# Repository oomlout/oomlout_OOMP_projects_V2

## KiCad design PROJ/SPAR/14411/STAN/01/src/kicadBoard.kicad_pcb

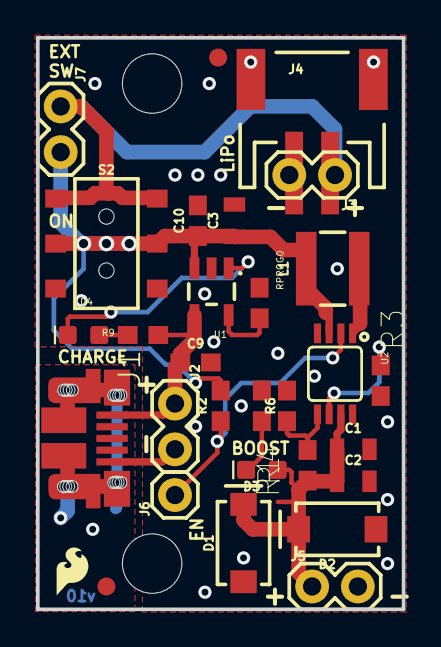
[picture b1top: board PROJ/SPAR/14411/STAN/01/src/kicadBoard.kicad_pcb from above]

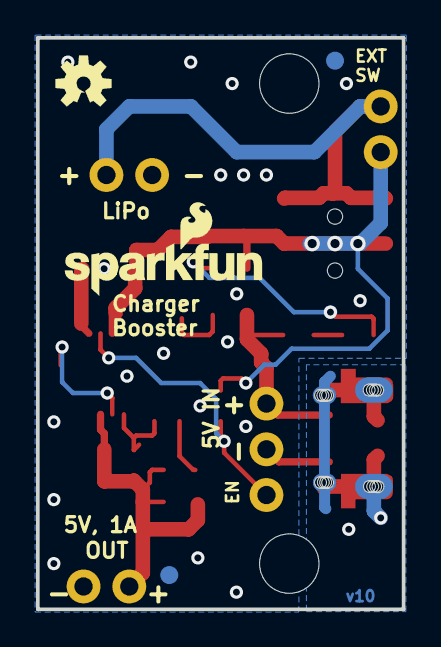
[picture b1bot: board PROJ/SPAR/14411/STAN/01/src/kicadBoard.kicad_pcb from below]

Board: 2 copper layers, 20.3 x 31.8 mm, 38 parts (5 on the bottom side), 14 nets.

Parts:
C1, C2, C3: 22uF; 0805
C9, C10: 4.7uF; 0603
D1, D2: 3A/40V/500mV; SMA-DIODE
D3: RED; LED-0603
D4: BLUE; LED-0603
FRAME1: FRAME-LETTER; CREATIVE_COMMONS
J1: AMP FCI 10103594-0001LF; USB-MICROB-PTH
J2, J3, J7: PTH; 1X02
J4: JST; JST-2-SMD
J5: 1X02
J6: 1X01
JP1, JP2, JP4, JP16: FIDUCIAL1X2; FIDUCIAL-1X2
JP3: SFE_LOGO_NAME_FLAME.1_INCH; SFE_LOGO_NAME_FLAME_.1
JP6, JP7: STAND-OFF
L1: 2.2UH3A; INDUCTOR_4X4MM
LOGO1: SFE_LOGO_FLAME.1_INCH; SFE_LOGO_FLAME_.1
R1: 100k; 0603
R2, R4: 750K; 0603
R3: DNP; 0603
R6: 4.7k; 0603
R9: 1k; 0603
RPROG0: 2.0k; 0603
S2: SWITCH_DPDT_SMD_AYZ0202
TP1: TEST-POINT3; PAD.03X.03
U1: MCP73831; SOT23-5
U2: PAM2401; MSOP8
U$1: OSHW-LOGOS; OSHW-LOGO-S

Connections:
5VIN: C9.1, J1.VBUS, J2.1, R9.2, U1.4
EN: J6.1, R2.1, U2.2
GND: C1.2, C2.2, C3.2, C9.2, C10.2, D1.A, D2.A, J1.GND, J2.2, J3.2, J4.1, J5.2, R1.1, R3.1, R6.1, RPROG0.2, U1.2, U2.4, U2.8
unnamed: D3.C, R6.2
unnamed: D4.A, R9.1
unnamed: L1.P$2, U2.1
unnamed: R3.2, U2.6
unnamed: J3.1, J4.2, J7.1, S2.1, S2.4
unnamed: RPROG0.1, U1.5
unnamed: R1.2, R4.1, U2.5
unnamed: D4.C, TP1.P$1, U1.1
SHIELD: J1.P$1, J1.P$2, J1.P$3, J1.P$4, J1.P$6, J1.P$8, J1.P$10, J1.P$12, J1.SHEILD2, J1.SHIELD, J1.SHIELD3, J1.SHIELD4
VBATT: C3.1, C10.1, J7.2, L1.P$1, R2.2, S2.2, S2.5, U1.3, U2.3
VCC: C1.1, C2.1, D1.C, D2.C, D3.A, J5.1, R4.2, U2.7

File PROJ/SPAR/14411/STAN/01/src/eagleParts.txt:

Partlist

Exported from boardEagle.brd at 19/08/2022 23:57

EAGLE Version 9.6.2 Copyright (c) 1988-2020 Autodesk, Inc.

Assembly variant: 

Part     Value                   Package                 Library               Position (inch)       Orientation

C1       22uF                    0805                    SparkFun-Capacitors   (0.69 0.35)           R0
C2       22uF                    0805                    SparkFun-Capacitors   (0.69 0.28)           R0
C3       22uF                    0805                    SparkFun-Capacitors   (0.43 0.85)           R90
C9       4.7uF                   0603                    SparkFun-Capacitors   (0.345 0.54)          R0
C10      4.7uF                   0603                    SparkFun-Capacitors   (0.35 0.85)           R90
D1       3A/40V/500mV            SMA-DIODE               SparkFun-DiscreteSemi (0.45 0.145)          R90
D2       3A/40V/500mV            SMA-DIODE               SparkFun-DiscreteSemi (0.655 0.175)         R180
D3       RED                     LED-0603                SparkFun-LED          (0.49 0.305)          R180
D4       BLUE                    LED-0603                SparkFun-LED          (0.1 0.6)             R180
J1       AMP FCI 10103594-0001LF USB-MICROB-PTH          SparkFun-Connectors   (0.11 0.375)          R270
J2       PTH                     1X02                    SparkFun-Connectors   (0.3 0.45)            R270
J3       PTH                     1X02                    SparkFun-Connectors   (0.65 0.95)           R180
J4       JST                     JST-2-SMD               SparkFun-Connectors   (0.6 1.1)             R0
J5                               1X02                    SparkFun-Connectors   (0.6 0.05)            R0
J6                               1X01                    SparkFun-Connectors   (0.3 0.25)            R90
J7       PTH                     1X02                    SparkFun-Connectors   (0.05 1.1)            R270
JP1      FIDUCIAL1X2             FIDUCIAL-1X2            SparkFun-Aesthetics   (0.15 1.2)            MR0
JP2      FIDUCIAL1X2             FIDUCIAL-1X2            SparkFun-Aesthetics   (0.15 0.05)           R0
JP4      FIDUCIAL1X2             FIDUCIAL-1X2            SparkFun-Aesthetics   (0.5125 0.075)        MR0
JP16     FIDUCIAL1X2             FIDUCIAL-1X2            SparkFun-Aesthetics   (0.394375 1.206875)   R0
L1       2.2UH3A                 INDUCTOR_4X4MM          SparkFun-Coils        (0.645 0.745)         R90
R1       100k                    0603                    SparkFun-Resistors    (0.545 0.445)         R270
R2       750K                    0603                    SparkFun-Resistors    (0.4 0.445)           R90
R3       DNP                     0603                    SparkFun-Resistors    (0.75 0.5)            R90
R4       750K                    0603                    SparkFun-Resistors    (0.59 0.315)          R270
R6       4.7k                    0603                    SparkFun-Resistors    (0.49 0.445)          R270
R9       1k                      0603                    SparkFun-Resistors    (0.23 0.6)            R0
RPROG    2.0k                    0603                    SparkFun-Resistors    (0.485 0.67)          R90
S2                               SWITCH_DPDT_SMD_AYZ0202 SparkFun-Switches     (0.15 0.8)            R270
TP1      TEST-POINT3             PAD.03X.03              SparkFun-Connectors   (0.16 0.65)           MR0
U1       MCP73831                SOT23-5                 SparkFun-IC-Power     (0.38 0.695)          R180
U2       PAM2401                 MSOP8                   SparkFun-IC-Power     (0.65 0.515)          R180

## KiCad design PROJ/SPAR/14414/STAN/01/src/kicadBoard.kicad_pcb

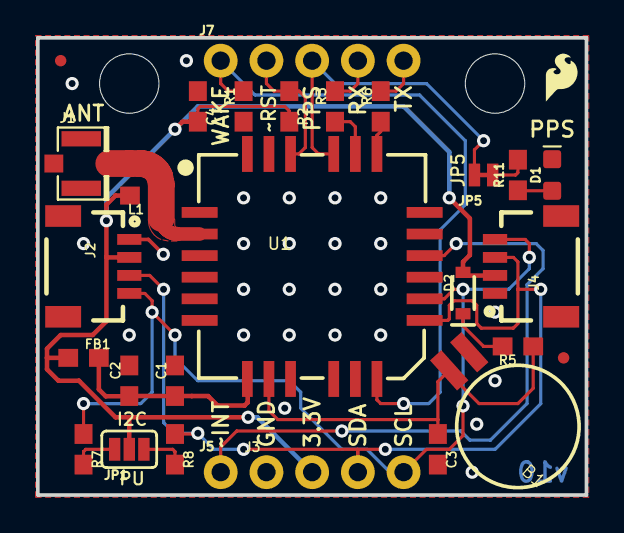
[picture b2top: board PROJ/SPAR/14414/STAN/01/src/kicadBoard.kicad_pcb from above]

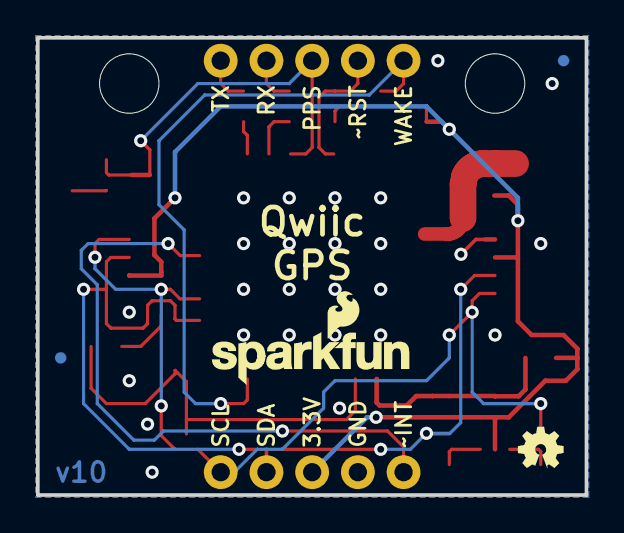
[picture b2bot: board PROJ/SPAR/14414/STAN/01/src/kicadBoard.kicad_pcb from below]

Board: 2 copper layers, 30.5 x 25.4 mm, 38 parts (4 on the bottom side), 20 nets.

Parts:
B1: 6.8MM_COIN_CELL; BATTCON-6.8MM
C1: 0.1uF; 0603
C2, C3, C4: 1.0uF; 0603
D1: BLUE; LED-0603
D2: 0.5A/40V/420mV; SOD-323
FB1: 600Ohm/100MHz; 0603
FRAME1: FRAME-LETTER; CREATIVE_COMMONS
J1: U.FL
J2, J4: Qwiic Right Angle; 1X04_1MM_RA
J3: PTH; 1X04_NO_SILK
J5: 1X01_NO_SILK
J7: 1X05_NO_SILK
JP1: SMT-JUMPER_3_2-NC_PASTE_SILK
JP2, JP6, JP7, JP8: FIDUCIALUFIDUCIAL; MICRO-FIDUCIAL
JP3, JP4: STAND-OFF
JP5: SMT-JUMPER_2_NC_TRACE_NO-SILK
L1: 33nH/±5%/500mA; 0603
LOGO1: OSHW-LOGOMINI; OSHW-LOGO-MINI
LOGO2: SFE_LOGO_NAME_FLAME.1_INCH; SFE_LOGO_NAME_FLAME_.1
LOGO3: REVISION
R1, R2: 10k; 0603
R3, R6, R11: 470; 0603
R5: 1k; 0603
R7, R8: 4.7k; 0603
U1: Titan X1 GPS; TITAN_X1_GPS
U$2: SFE_LOGO_FLAME_.1
U$3: SPECIAL_INSTRUCTIONS-PRODUCTION; PRODUCTION_INSTRUCTIONS

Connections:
3.3V: C4.2, D2.A, FB1.1, J2.2, J3.2, J4.2, JP1.2, L1.2, R2.2
BACKUP: B1.+, C3.1, R5.1, U1.8
EXT_ANT: J1.FEED, L1.1, U1.2
GND: B1.-, C1.2, C2.2, C3.2, C4.1, D1.C, J1.1, J1.2, J2.1, J3.1, J4.1, R1.1, U1.1, U1.3, U1.4, U1.5, U1.6, U1.9, U1.10, U1.11, U1.24
INT: J5.1, U1.16
unnamed: D1.A, R11.1
unnamed: JP5.1, R11.2
unnamed: JP1.1, R8.2
unnamed: D2.C, R5.2
unnamed: JP1.3, R7.2
PPS: J7.3, JP5.2, U1.21
RX: J7.4, R3.2
RXLV: R3.1, U1.20
SCL: J2.4, J3.4, J4.4, R7.1, U1.14
SDA: J2.3, J3.3, J4.3, R8.1, U1.13
TX: J7.5, R6.2
TXLV: R6.1, U1.19
VCC_FILTERED: C1.1, C2.1, FB1.2, U1.7
WAKE: J7.1, R1.2, U1.12
~RESET: J7.2, R2.1, U1.22

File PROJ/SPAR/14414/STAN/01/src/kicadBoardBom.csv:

"Id";"Designator";"Package";"Quantity";"Designation";"Supplier and ref";
1;"JP1";"SMT-JUMPER_3_2-NC_PASTE_SILK";1;"";;;
2;"R11,R6,R3";"0603";3;"470";;;
3;"JP6,JP2,JP7,JP8";"MICRO-FIDUCIAL";4;"FIDUCIALUFIDUCIAL";;;
4;"L1";"0603";1;"33nH/±5%/500mA";;;
5;"U$3";"PRODUCTION_INSTRUCTIONS";1;"SPECIAL_INSTRUCTIONS-PRODUCTION";;;
6;"U$2";"SFE_LOGO_FLAME_.1";1;"";;;
7;"J1";"U.FL";1;"U.FL";;;
8;"J4,J2";"1X04_1MM_RA";2;"Qwiic Right Angle";;;
9;"D1";"LED-0603";1;"BLUE";;;
10;"R1,R2";"0603";2;"10k";;;
11;"C3,C2,C4";"0603";3;"1.0uF";;;
12;"LOGO3";"REVISION";1;"REVISION";;;
13;"R8,R7";"0603";2;"4.7k";;;
14;"FRAME1";"CREATIVE_COMMONS";1;"FRAME-LETTER";;;
15;"B1";"BATTCON-6.8MM";1;"6.8MM_COIN_CELL";;;
16;"U1";"TITAN_X1_GPS";1;"Titan X1 GPS";;;
17;"JP5";"SMT-JUMPER_2_NC_TRACE_NO-SILK";1;"";;;
18;"J5";"1X01_NO_SILK";1;"";;;
19;"JP4,JP3";"STAND-OFF";2;"STAND-OFF";;;
20;"R5";"0603";1;"1k";;;
21;"J3";"1X04_NO_SILK";1;"PTH";;;
22;"C1";"0603";1;"0.1uF";;;
23;"FB1";"0603";1;"600Ohm/100MHz";;;
24;"J7";"1X05_NO_SILK";1;"";;;
25;"D2";"SOD-323";1;"0.5A/40V/420mV";;;
26;"LOGO2";"SFE_LOGO_NAME_FLAME_.1";1;"SFE_LOGO_NAME_FLAME.1_INCH";;;
27;"LOGO1";"OSHW-LOGO-MINI";1;"OSHW-LOGOMINI";;;

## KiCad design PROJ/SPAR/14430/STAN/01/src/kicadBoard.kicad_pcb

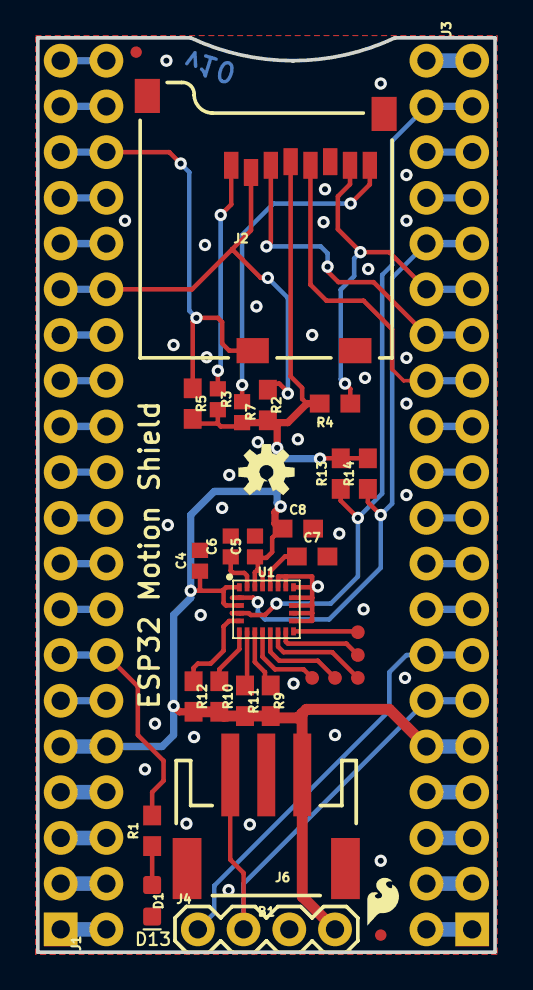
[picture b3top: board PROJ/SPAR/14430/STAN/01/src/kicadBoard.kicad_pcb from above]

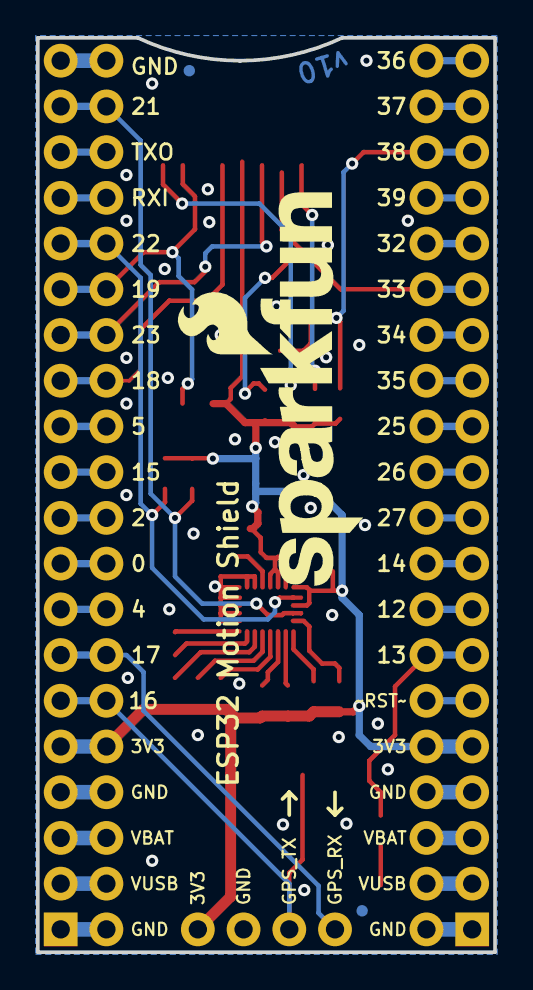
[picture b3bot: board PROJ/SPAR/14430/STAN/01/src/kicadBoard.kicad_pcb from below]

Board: 2 copper layers, 25.4 x 50.8 mm, 38 parts (3 on the bottom side), 49 nets.

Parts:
B1: ESP32_THING_WO_ANT_KEEPOUT; ESP32_THING_NO_ANT
C4, C5, C6: 0.1uF; 0402
C7: 10nF; 0603
C8: 10uF; 0603
D1: BLUE; LED-0603
FD1, FD2, FD3, FD4: FIDUCIALUFIDUCIAL; FIDUCIAL-MICRO
FRAME1: FRAME-LETTER; CREATIVE_COMMONS
J1, J3: 1X20_NOSILK
J2: MICRO-SD_CARD_SOCKET; MICRO-SD-SOCKET
J4: 1X04
J6: 3-PIN SMD; JST-3-SMD
LOGO1: OSHW-LOGOS; OSHW-LOGO-S
LOGO2: SFE_LOGO_NAME_FLAME.2_INCH; SFE_LOGO_NAME_FLAME_.2
LOGO3: SFE_LOGO_FLAME.1_INCH; SFE_LOGO_FLAME_.1
R1: 470; 0603
R2, R4, R5, R9, R10, R11, R12: 10k; 0603
R3, R7: 100K; 0402
R13, R14: 4.7k; 0603
TP1, TP2, TP3, TP4, TP5: TEST-POINT3; PAD.03X.03
U1: LSM9DS1; LGA-24-3.5X3

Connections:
3.3V: B1.5, B1.36, C4.1, C5.1, C8.1, J1.5, J2.VCC, J3.16, J4.4, J6.3, R2.2, R3.2, R4.2, R5.2, R7.2, R9.2, R10.2, R11.2, R12.2, R13.2, R14.2, U1.1, U1.3, U1.22, U1.23
C1: C6.1, U1.24
CAP: C7.1, U1.21
CS_A/G: R11.1, U1.7
CS_M: R9.1, U1.8
DEN_A/G: TP3.P$1, U1.13
DRDY_M: TP4.P$1, U1.9
GND: B1.1, B1.4, B1.21, B1.37, B1.40, C4.2, C5.2, C6.2, C7.2, C8.2, D1.C, J1.1, J1.4, J2.GND, J2.GND1, J2.GND3, J3.1, J3.17, J3.20, J4.3, J6.2, U1.14, U1.15, U1.16, U1.17, U1.18, U1.19, U1.20
GPS_LED: B1.7, J1.7, R1.2
GPS_RX: B1.34, J3.14, J4.1
GPS_TX: B1.35, J3.15, J4.2, J6.1
INT1_A/G: TP1.P$1, U1.11
INT2_A/G: TP2.P$1, U1.12
INT_M: TP5.P$1, U1.10
unnamed: D1.A, R1.1
unnamed: B1.30, J3.10
unnamed: B1.17, J1.17
unnamed: B1.16, J1.16
unnamed: B1.19, J1.19
unnamed: B1.10, J1.10
unnamed: B1.14, J1.14
unnamed: J2.RSV1, R3.1
unnamed: J2.RSV2, R7.1
unnamed: B1.6, J1.6
unnamed: B1.8, J1.8
unnamed: B1.9, J1.9
unnamed: B1.11, J1.11
unnamed: B1.12, J1.12
unnamed: B1.13, J1.13
unnamed: B1.20, J1.20
unnamed: B1.23, J3.3
unnamed: B1.24, J3.4
unnamed: B1.29, J3.9
unnamed: B1.31, J3.11
unnamed: B1.32, J3.12
unnamed: B1.33, J3.13
SCL: B1.25, J3.5, R14.1, U1.2
SDA: B1.22, J3.2, R13.1, U1.4
SDO_A/G: R12.1, U1.5
SDO_M: R10.1, U1.6
SD_CD: B1.18, J1.18, J2.CD2, R5.1
SD_CS: B1.15, J1.15, J2.CS, R2.1
SD_DI: B1.27, J2.DI, J3.7
SD_DO: B1.26, J2.DO, J3.6, R4.1
SD_SCK: B1.28, J2.SCLK, J3.8
VUSB: B1.39, J3.19
VUSB_B: B1.2, J1.2
V_BATT: B1.38, J3.18
V_BATT_B: B1.3, J1.3

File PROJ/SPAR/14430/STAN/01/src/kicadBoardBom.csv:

"Id";"Designator";"Package";"Quantity";"Designation";"Supplier and ref";
1;"LOGO3";"SFE_LOGO_FLAME_.1";1;"SFE_LOGO_FLAME.1_INCH";;;
2;"B1";"ESP32_THING_NO_ANT";1;"ESP32_THING_WO_ANT_KEEPOUT";;;
3;"R10,R11,R4,R5,R12,R9,R2";"0603";7;"10k";;;
4;"C8";"0603";1;"10uF";;;
5;"TP2,TP4,TP5,TP1,TP3";"PAD.03X.03";5;"TEST-POINT3";;;
6;"FRAME1";"CREATIVE_COMMONS";1;"FRAME-LETTER";;;
7;"D1";"LED-0603";1;"BLUE";;;
8;"R1";"0603";1;"470";;;
9;"C5,C4,C6";"0402";3;"0.1uF";;;
10;"R7,R3";"0402";2;"100K";;;
11;"U1";"LGA-24-3.5X3";1;"LSM9DS1";;;
12;"C7";"0603";1;"10nF";;;
13;"R13,R14";"0603";2;"4.7k";;;
14;"J2";"MICRO-SD-SOCKET";1;"MICRO-SD_CARD_SOCKET";;;
15;"FD1,FD2,FD3,FD4";"FIDUCIAL-MICRO";4;"FIDUCIALUFIDUCIAL";;;
16;"J4";"1X04";1;"";;;
17;"J1,J3";"1X20_NOSILK";2;"";;;
18;"J6";"JST-3-SMD";1;"3-PIN SMD";;;
19;"LOGO1";"OSHW-LOGO-S";1;"OSHW-LOGOS";;;
20;"LOGO2";"SFE_LOGO_NAME_FLAME_.2";1;"SFE_LOGO_NAME_FLAME.2_INCH";;;

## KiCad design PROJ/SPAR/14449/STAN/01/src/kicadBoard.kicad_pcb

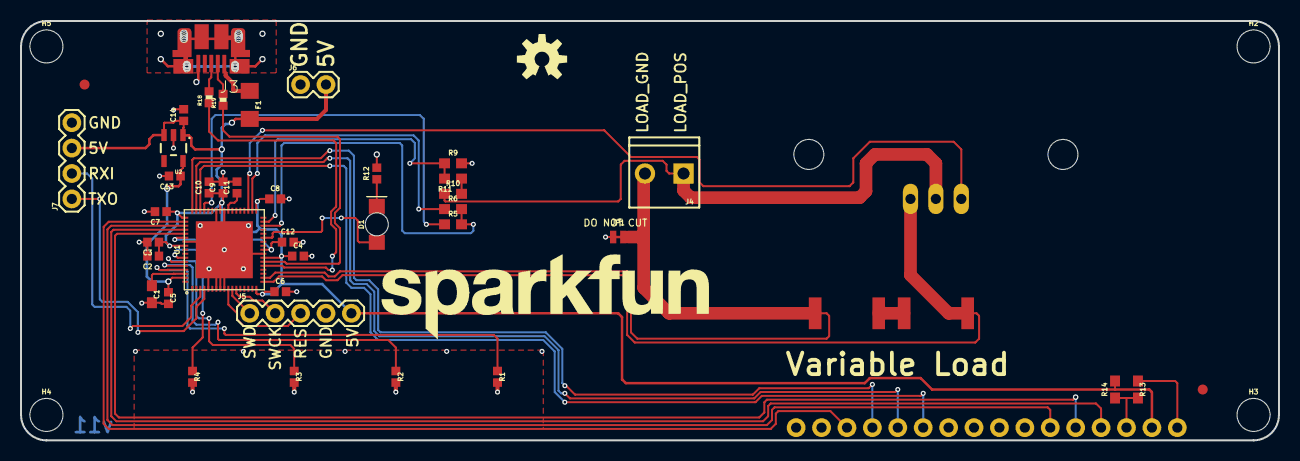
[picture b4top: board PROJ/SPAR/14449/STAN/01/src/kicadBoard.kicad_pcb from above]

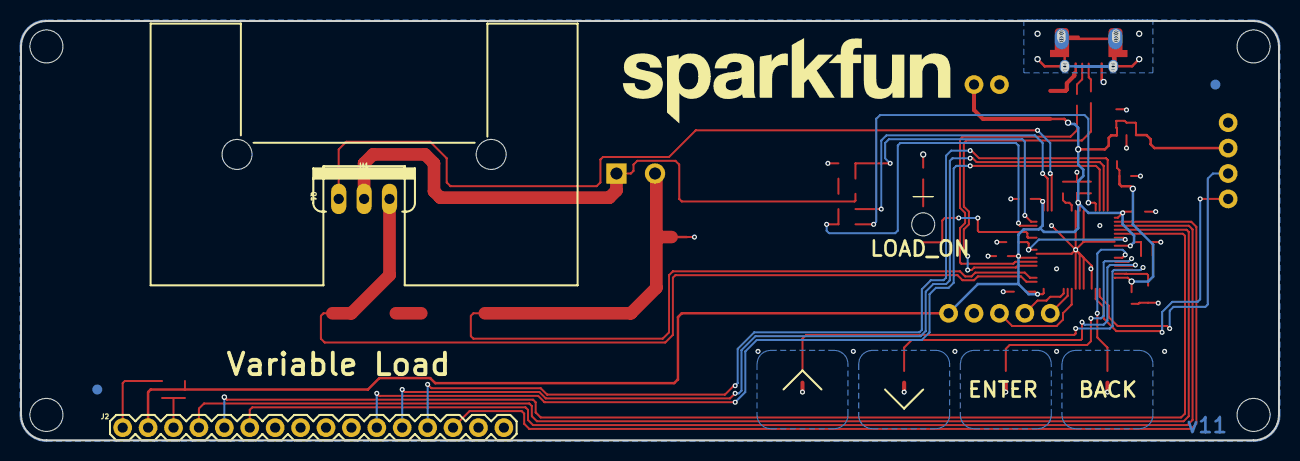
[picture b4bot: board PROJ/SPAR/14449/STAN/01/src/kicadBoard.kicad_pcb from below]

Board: 4 copper layers, 125.7 x 41.9 mm, 55 parts (6 on the bottom side), 41 nets.

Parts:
C1: 2.2nF; 0603
C2, C4, C5, C6, C7, C8, C9: 0.1uF; 0402
C3, C10, C11, C12, C13, C14: 1.0uF; 0402
D1: GREEN; LED-1206-BOTTOM
F1: 6V/0.5A; 1206
FD1, FD2, FD3, FD4: FIDUCIAL1X2; FIDUCIAL-1X2
FRAME1: FRAME-LETTER; CREATIVE_COMMONS
H1: 6400BG_HEATSINK
H2, H3, H4, H5: STAND-OFF
J2: 1X16
J3: AMP FCI 10103594-0001LF; USB-MICROB-PTH
J4: SCREWTERMINAL-3.5MM-2_LOCK
J5: 1X05
J6: 1X02
J7: 1X04
JP1: JUMPER-SMT_2_NC_TRACE_NO-SILK; SMT-JUMPER_2_NC_TRACE_NO-SILK
LOGO1: OSHW-LOGOM; OSHW-LOGO-M
LOGO2, LOGO3: SFE_LOGO_NAME.3_INCH; SFE_LOGO_NAME_.3
Q1: 60V/32A/35mΩ; TO220V
R1, R2, R3, R4, R12: 560; 0402
R5, R6: 47k; 0603
R7, R8: 0.05; 2512
R9, R13: 1k; 0603
R10: 8.2k; 0603
R11: 787; 0603
R14: 4.7k; 0603
R18, R19: 22; 0402-RES
U1: CY8C5868LTI-LP039; QFN-68
U2: 3.3V; SOT23-5

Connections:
3.3V: C5.1, C13.1, U1.67, U2.5
5V: C2.1, C3.1, C4.1, C6.1, C7.1, C8.1, C9.1, C10.1, C14.1, F1.2, J2.2, J5.5, J6.2, J7.3, R14.2, U1.17, U1.24, U1.35, U1.44, U1.52, U1.59, U2.1, U2.3
CONTRAST: J2.3, R13.2, R14.1
D+: J3.D+, R18.2
D-: J3.D-, R19.2
GND: C1.2, C2.2, C3.2, C4.2, C5.2, C6.2, C7.2, C8.2, C9.2, C10.2, C11.2, C12.2, C13.2, C14.2, J2.1, J3.GND, J5.4, J6.1, J7.4, JP1.1, R9.2, R12.2, R13.1, U1.5, U1.7, U1.8, U1.9, U1.25, U1.43, U1.45, U1.58, U1.69, U2.2
GND-ISO: J4.2, JP1.2, R8.P$1, U1.19
I_SENSE_HIGH: Q1.3, R7.P$2, U1.18
I_SET: Q1.1, U1.37
I_SET_SUM: R5.2, R6.2, U1.32
LCD_D4: J2.11, U1.49
LCD_D5: J2.12, U1.50
LCD_D6: J2.13, U1.51
LCD_D7: J2.14, U1.53
LCD_E: J2.6, U1.54
LCD_RS: J2.4, U1.55
LCD_RW: J2.5, U1.56
unnamed: R1.1, U1.65
unnamed: R2.1, U1.64
unnamed: R3.1, U1.63
unnamed: R4.1, U1.62
unnamed: C1.1, U1.66
unnamed: C12.1, U1.26, U1.57
unnamed: C11.1, U1.42
unnamed: R18.1, U1.22
unnamed: R19.1, U1.23
unnamed: R5.1, U1.48
unnamed: R6.1, U1.36
unnamed: D1.A, U1.29
unnamed: D1.C, R12.1
unnamed: F1.1, J3.VBUS
unnamed: J4.1, Q1.2, R10.1
unnamed: R10.2, R11.1
unnamed: R7.P$1, R8.P$2
RXI: J7.2, U1.3
SHIELD: J3.P$1, J3.P$2, J3.P$3, J3.P$4, J3.P$6, J3.P$8, J3.P$10, J3.P$12, J3.SHEILD2, J3.SHIELD, J3.SHIELD3, J3.SHIELD4
SWDCK: J5.2, U1.12
SWDIO: J5.1, U1.11
TXO: J7.1, U1.4
V_SENSE: R9.1, R11.2, U1.33
XRES: J5.3, U1.10

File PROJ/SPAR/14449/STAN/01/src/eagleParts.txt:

Partlist

Exported from boardEagle.brd at 20/08/2022 00:05

EAGLE Version 9.6.2 Copyright (c) 1988-2020 Autodesk, Inc.

Assembly variant: 

Part     Value                         Package                       Library                     Position (inch)       Orientation

C1       2.2nF                         0603                          SparkFun-Capacitors         (0.515 0.575)         R270
C2       0.1uF                         0402                          SparkFun-Capacitors         (0.52 0.725)          R180
C3       1.0uF                         0402                          SparkFun-Capacitors         (0.52 0.78)           R180
C4       0.1uF                         0402                          SparkFun-Capacitors         (1.09 0.725)          R0
C5       0.1uF                         0402                          SparkFun-Capacitors         (0.58 0.56)           R270
C6       0.1uF                         0402                          SparkFun-Capacitors         (1.02 0.585)          R0
C7       0.1uF                         0402                          SparkFun-Capacitors         (0.55 0.9)            R180
C8       0.1uF                         0402                          SparkFun-Capacitors         (1 0.95)              R0
C9       0.1uF                         0402                          SparkFun-Capacitors         (0.795 0.995)         R90
C10      1.0uF                         0402                          SparkFun-Capacitors         (0.74 0.995)          R90
C11      1.0uF                         0402                          SparkFun-Capacitors         (0.85 0.995)          R90
C12      1.0uF                         0402                          SparkFun-Capacitors         (1.05 0.78)           R0
C13      1.0uF                         0402                          SparkFun-Capacitors         (0.605 1.04)          R180
C14      1.0uF                         0402                          SparkFun-Capacitors         (0.64 1.28)           R90
D1       GREEN                         LED-1206-BOTTOM               SparkFun-LED                (1.4 0.85)            R90
F1       6V/0.5A                       1206                          SparkFun-Fuses              (0.9 1.32)            R270
FD1      FIDUCIAL1X2                   FIDUCIAL-1X2                  SparkFun-Aesthetics         (4.65 0.2)            MR0
FD2      FIDUCIAL1X2                   FIDUCIAL-1X2                  SparkFun-Aesthetics         (0.25 1.4)            MR0
FD3      FIDUCIAL1X2                   FIDUCIAL-1X2                  SparkFun-Aesthetics         (4.65 0.2)            R0
FD4      FIDUCIAL1X2                   FIDUCIAL-1X2                  SparkFun-Aesthetics         (0.25 1.4)            R0
J2                                     1X16                          SparkFun-Connectors         (4.55 0.05)           MR0
J3       AMP FCI 10103594-0001LF       USB-MICROB-PTH                SparkFun-Connectors         (0.75 1.535)          R180
J4                                     SCREWTERMINAL-3.5MM-2_LOCK    SparkFun-Connectors         (2.6 1.05)            R180
J5                                     1X05                          SparkFun-Connectors         (0.9 0.5)             R0
J6                                     1X02                          SparkFun-Connectors         (1.1 1.4)             R0
J7                                     1X04                          SparkFun-Connectors         (0.2 0.95)            R90
JP1      JUMPER-SMT_2_NC_TRACE_NO-SILK SMT-JUMPER_2_NC_TRACE_NO-SILK SparkFun-Jumpers            (2.35 0.8)            R0
Q1       60V/32A/35m?                  TO220V                        SparkFun-DiscreteSemi       (3.6 0.95)            MR0
R1       560                           0402                          SparkFun-Resistors          (1.875 0.25)          R270
R2       560                           0402                          SparkFun-Resistors          (1.475 0.25)          R270
R3       560                           0402                          SparkFun-Resistors          (1.075 0.25)          R270
R4       560                           0402                          SparkFun-Resistors          (0.675 0.25)          R270
R5       47k                           0603                          SparkFun-Resistors          (1.7 0.85)            R0
R6       47k                           0603                          SparkFun-Resistors          (1.7 0.91)            R0
R7       0.05                          2512                          SparkFun-Resistors          (3.6 0.5)             R0
R8       0.05                          2512                          SparkFun-Resistors          (3.25 0.5)            R0
R9       1k                            0603                          SparkFun-Resistors          (1.7 1.09)            R0
R10      8.2k                          0603                          SparkFun-Resistors          (1.7 0.97)            R0
R11      787                           0603                          SparkFun-Resistors          (1.7 1.03)            R180
R12      560                           0402                          SparkFun-Resistors          (1.4 1.05)            R90
R13      1k                            0603                          SparkFun-Resistors          (4.395 0.2)           R270
R14      4.7k                          0603                          SparkFun-Resistors          (4.305 0.2)           R90
R18      22                            0402-RES                      SparkFun-Resistors          (0.74 1.35)           R90
R19      22                            0402-RES                      SparkFun-Resistors          (0.795 1.34)          R90
U1       CY8C5868LTI-LP039             QFN-68                        SparkFun-IC-Microcontroller (0.8 0.75)            R90
U2       3.3V                          SOT23-5                       SparkFun-IC-Power           (0.6 1.15)            R180

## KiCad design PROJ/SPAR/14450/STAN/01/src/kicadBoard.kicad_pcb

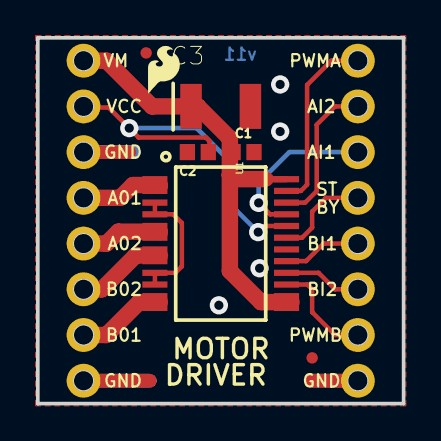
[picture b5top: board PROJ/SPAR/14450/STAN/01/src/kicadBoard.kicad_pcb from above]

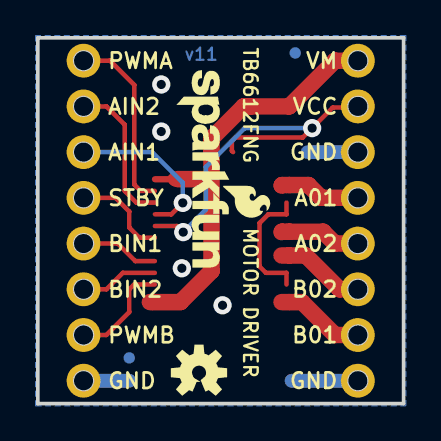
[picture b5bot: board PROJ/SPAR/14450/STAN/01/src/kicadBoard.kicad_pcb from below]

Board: 16 copper layers, 20.3 x 20.3 mm, 14 parts (4 on the bottom side), 14 nets.

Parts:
C1, C2: 0.1uF; 0402
C3: 10uF; EIA3528
FD1, FD2, FD3, FD4: FIDUCIALUFIDUCIAL; FIDUCIAL-MICRO
FRAME1: FRAME-LETTER; CREATIVE_COMMONS
JP1, JP2: 1X08_OFFSET_REDUCED
LOGO1: SFE_LOGO_FLAME.1_INCH; SFE_LOGO_FLAME_.1
LOGO2: OSHW-LOGOS; OSHW-LOGO-S
LOGO4: SFE_LOGO_NAME_FLAME.1_INCH; SFE_LOGO_NAME_FLAME_.1
U1: TB6612FNG; SSOP24

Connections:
A01: JP1.5, U1.1, U1.2
A02: JP1.4, U1.5, U1.6
AIN1: JP2.3, U1.21
AIN2: JP2.2, U1.22
B01: JP1.2, U1.11, U1.12
B02: JP1.3, U1.7, U1.8
BIN1: JP2.5, U1.17
BIN2: JP2.6, U1.16
GND: C1.2, C2.2, C3.C, JP1.1, JP1.6, JP2.8, U1.3, U1.4, U1.9, U1.10, U1.18
PWMA: JP2.1, U1.23
PWMB: JP2.7, U1.15
STBY: JP2.4, U1.19
VCC: C2.1, JP1.7, U1.20
VM: C1.1, C3.A, JP1.8, U1.13, U1.14, U1.24

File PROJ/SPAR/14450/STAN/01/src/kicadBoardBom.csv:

"Id";"Designator";"Package";"Quantity";"Designation";"Supplier and ref";
1;"LOGO1";"SFE_LOGO_FLAME_.1";1;"SFE_LOGO_FLAME.1_INCH";;;
2;"JP2,JP1";"1X08_OFFSET_REDUCED";2;"";;;
3;"C1,C2";"0402";2;"0.1uF";;;
4;"FD2,FD4,FD1,FD3";"FIDUCIAL-MICRO";4;"FIDUCIALUFIDUCIAL";;;
5;"FRAME1";"CREATIVE_COMMONS";1;"FRAME-LETTER";;;
6;"C3";"EIA3528";1;"10uF";;;
7;"U1";"SSOP24";1;"TB6612FNG";;;
8;"LOGO2";"OSHW-LOGO-S";1;"OSHW-LOGOS";;;
9;"LOGO4";"SFE_LOGO_NAME_FLAME_.1";1;"SFE_LOGO_NAME_FLAME.1_INCH";;;

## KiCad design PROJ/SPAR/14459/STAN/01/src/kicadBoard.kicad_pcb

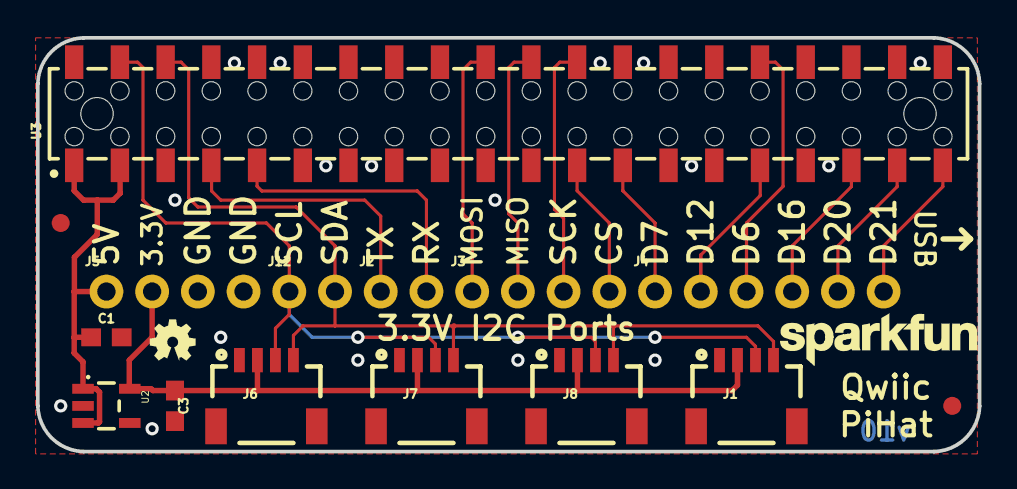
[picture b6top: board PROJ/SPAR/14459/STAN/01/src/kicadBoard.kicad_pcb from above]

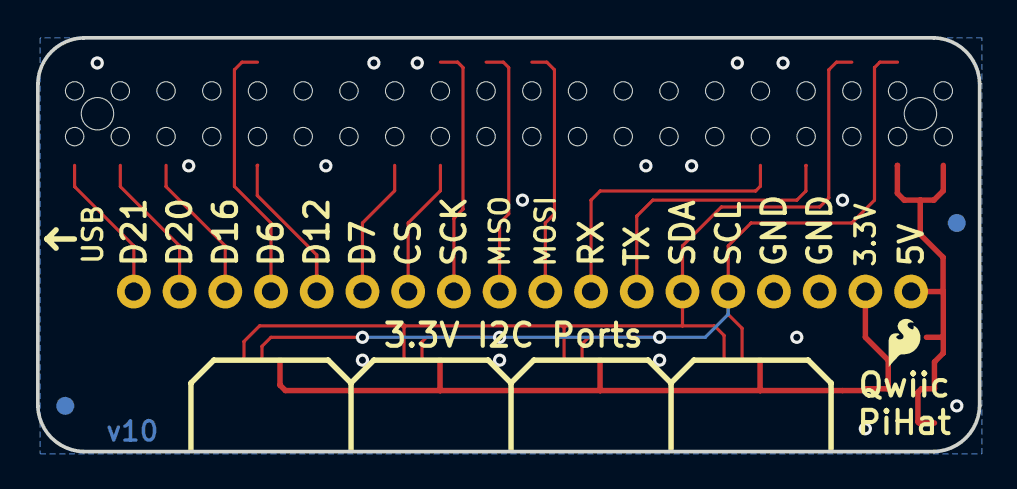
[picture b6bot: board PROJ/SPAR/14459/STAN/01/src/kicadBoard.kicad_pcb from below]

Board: 2 copper layers, 52.3 x 23.0 mm, 22 parts (3 on the bottom side), 17 nets.

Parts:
C1, C3: 1.0uF; 0603
FD1, FD2, FD3, FD4: FIDUCIAL1X2; FIDUCIAL-1X2
FRAME1: FRAME-LETTER; CREATIVE_COMMONS
J1, J6, J7, J8: Qwiic Right Angle; 1X04_1MM_RA
J2, J12: 1X02_NO_SILK
J3, J5: 1X04_NO_SILK
J4: 1X06_NO_SILK
LOGO1: OSHW-LOGOMINI; OSHW-LOGO-MINI
LOGO2: REVISION
U2: 3.3V/600mA; SOT23-5
U3: RASPBERRY_PI_SHIELD_BOTTOM_ENTRY_NOHOLES
U$1: SFE_LOGO_FLAME.1_INCH; SFE_LOGO_FLAME_.1
U$2: SFE_LOGO_NAME.1_INCH; SFE_LOGO_NAME_.1

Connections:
3.3V: C3.1, J1.2, J5.2, J6.2, J7.2, J8.2, U2.5
5V: C1.1, J5.1, U2.1, U2.3, U3.2, U3.4
CS: J3.4, U3.24
D6: J4.3, U3.31
D7: J4.1, U3.26
D12: J4.2, U3.32
D16: J4.4, U3.36
D20: J4.5, U3.38
D21: J4.6, U3.40
GND: C1.2, C3.2, J1.1, J5.3, J5.4, J6.1, J7.1, J8.1, U2.2, U3.6, U3.9, U3.14, U3.20, U3.25, U3.30, U3.34, U3.39
MISO: J3.2, U3.21
MOSI: J3.1, U3.19
RX: J2.2, U3.10
SCK: J3.3, U3.23
SCL: J1.4, J6.4, J7.4, J8.4, J12.2, U3.5
SDA: J1.3, J6.3, J7.3, J8.3, J12.1, U3.3
TX: J2.1, U3.8

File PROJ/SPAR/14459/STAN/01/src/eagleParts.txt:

Partlist

Exported from boardEagle.brd at 20/08/2022 00:10

EAGLE Version 9.6.2 Copyright (c) 1988-2020 Autodesk, Inc.

Assembly variant: 

Part     Value             Package                                  Library             Position (inch)       Orientation

C1       1.0uF             0603                                     SparkFun-Capacitors (0.15 0.25)           R0
C3       1.0uF             0603                                     SparkFun-Capacitors (0.3 0.1)             R270
FD1      FIDUCIAL1X2       FIDUCIAL-1X2                             SparkFun-Aesthetics (0.05 0.5)            R180
FD2      FIDUCIAL1X2       FIDUCIAL-1X2                             SparkFun-Aesthetics (2 0.1)               R180
FD3      FIDUCIAL1X2       FIDUCIAL-1X2                             SparkFun-Aesthetics (2 0.1)               MR0
FD4      FIDUCIAL1X2       FIDUCIAL-1X2                             SparkFun-Aesthetics (0.05 0.5)            MR0
J1       Qwiic Right Angle 1X04_1MM_RA                              SparkFun-Connectors (1.55003076 0.20000468) R0
J2                         1X02_NO_SILK                             SparkFun-Connectors (0.75 0.35)           R0
J3                         1X04_NO_SILK                             SparkFun-Connectors (0.95 0.35)           R0
J4                         1X06_NO_SILK                             SparkFun-Connectors (1.35 0.35)           R0
J5                         1X04_NO_SILK                             SparkFun-Connectors (0.15 0.35)           R0
J6       Qwiic Right Angle 1X04_1MM_RA                              SparkFun-Connectors (0.5 0.2)             R0
J7       Qwiic Right Angle 1X04_1MM_RA                              SparkFun-Connectors (0.85 0.2)            R0
J8       Qwiic Right Angle 1X04_1MM_RA                              SparkFun-Connectors (1.2 0.2)             R0
J12                        1X02_NO_SILK                             SparkFun-Connectors (0.55 0.35)           R0
U2       3.3V/600mA        SOT23-5                                  SparkFun-IC-Power   (0.15 0.1)            R270
U3                         RASPBERRY_PI_SHIELD_BOTTOM_ENTRY_NOHOLES SparkFun-Connectors (-0.25 0.55)          R0

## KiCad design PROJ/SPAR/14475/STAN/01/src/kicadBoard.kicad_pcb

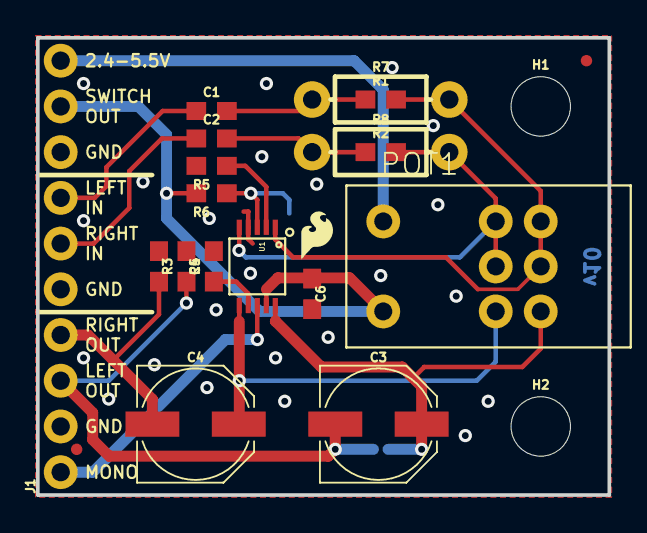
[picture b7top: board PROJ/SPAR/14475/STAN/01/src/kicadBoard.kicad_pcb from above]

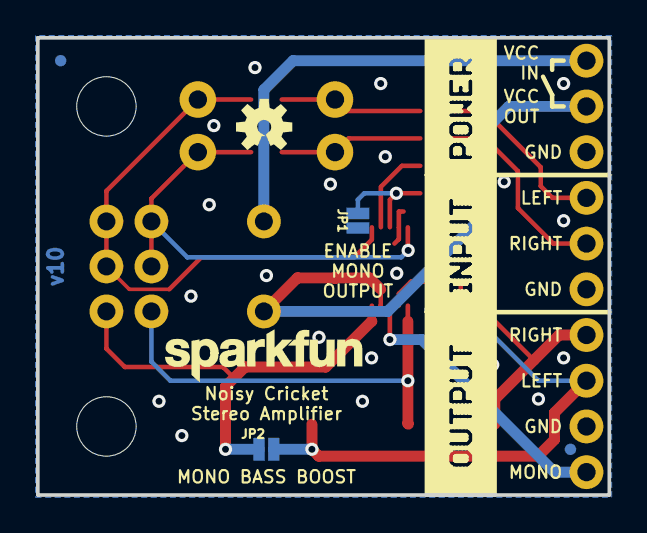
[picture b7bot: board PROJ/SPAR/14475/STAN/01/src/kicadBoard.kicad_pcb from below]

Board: 2 copper layers, 31.8 x 25.4 mm, 29 parts (6 on the bottom side), 17 nets.

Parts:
C1, C2, C5, C6: 1.0uF; 0603
C3, C4: 100uF; PANASONIC_D
FD1, FD2, FD3, FD4: FIDUCIALUFIDUCIAL; FIDUCIAL-MICRO
FRAME1: FRAME-LETTER; CREATIVE_COMMONS
H1, H2: STAND-OFF
J1: 1X10_NO_SILK
JP1, JP2: SMT-JUMPER_2_NO_NO-SILK
LOGO1: SFE_LOGO_NAME.1_INCH; SFE_LOGO_NAME_.1
LOGO2: OSHW-LOGOS; OSHW-LOGO-S
POT1: 20k; POT-DUAL-SWITCH-PTH
R1, R2: 2.2k; 0603
R3, R4: 1k; 0603
R5, R6: 100k; 0603
R7, R8: AXIAL-0.3-KIT
U1: LM4853; TFSOP-10
U$1: SFE_LOGO_FLAME_.1

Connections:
5V: C6.1, J1.9, POT1.SW2, R6.2, U1.VDD
GND: C5.2, C6.2, J1.2, J1.5, J1.8, JP1.1, R3.1, R4.1, R5.2, U1.GND
LIN: C1.1, J1.7
LOUT: C3.-, J1.3, JP2.2, R4.2
LOUT+: C3.+, JP2.1, POT1.A3, U1.LOUT
MODE: JP1.2, R6.1, U1.HP-IN
MONO_OUT: J1.1, U1.BTL
unnamed: C1.2, R1.1, R7.P$1
unnamed: C5.1, U1.BP
unnamed: C2.2, R2.1, R8.P$1
unnamed: R5.1, U1.SDN
unnamed: C4.+, POT1.B3, U1.ROUT
unnamed: POT1.A1, POT1.A2, R1.2, R7.P$2, U1.LIN
unnamed: POT1.B1, POT1.B2, R2.2, R8.P$2, U1.RIN
RIN: C2.1, J1.6
ROUT: C4.-, J1.4, R3.2
VIN: J1.10, POT1.SW1

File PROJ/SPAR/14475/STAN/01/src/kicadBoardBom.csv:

"Id";"Designator";"Package";"Quantity";"Designation";"Supplier and ref";
1;"C1,C6,C5,C2";"0603";4;"1.0uF";;;
2;"R3,R4";"0603";2;"1k";;;
3;"U$1";"SFE_LOGO_FLAME_.1";1;"";;;
4;"R1,R2";"0603";2;"2.2k";;;
5;"FD1,FD2,FD3,FD4";"FIDUCIAL-MICRO";4;"FIDUCIALUFIDUCIAL";;;
6;"R5,R6";"0603";2;"100k";;;
7;"C4,C3";"PANASONIC_D";2;"100uF";;;
8;"POT1";"POT-DUAL-SWITCH-PTH";1;"20k";;;
9;"R7,R8";"AXIAL-0.3-KIT";2;" ";;;
10;"H2,H1";"STAND-OFF";2;"STAND-OFF";;;
11;"J1";"1X10_NO_SILK";1;"";;;
12;"U1";"TFSOP-10";1;"LM4853";;;
13;"FRAME1";"CREATIVE_COMMONS";1;"FRAME-LETTER";;;
14;"LOGO2";"OSHW-LOGO-S";1;"OSHW-LOGOS";;;
15;"JP2,JP1";"SMT-JUMPER_2_NO_NO-SILK";2;"";;;
16;"LOGO1";"SFE_LOGO_NAME_.1";1;"SFE_LOGO_NAME.1_INCH";;;

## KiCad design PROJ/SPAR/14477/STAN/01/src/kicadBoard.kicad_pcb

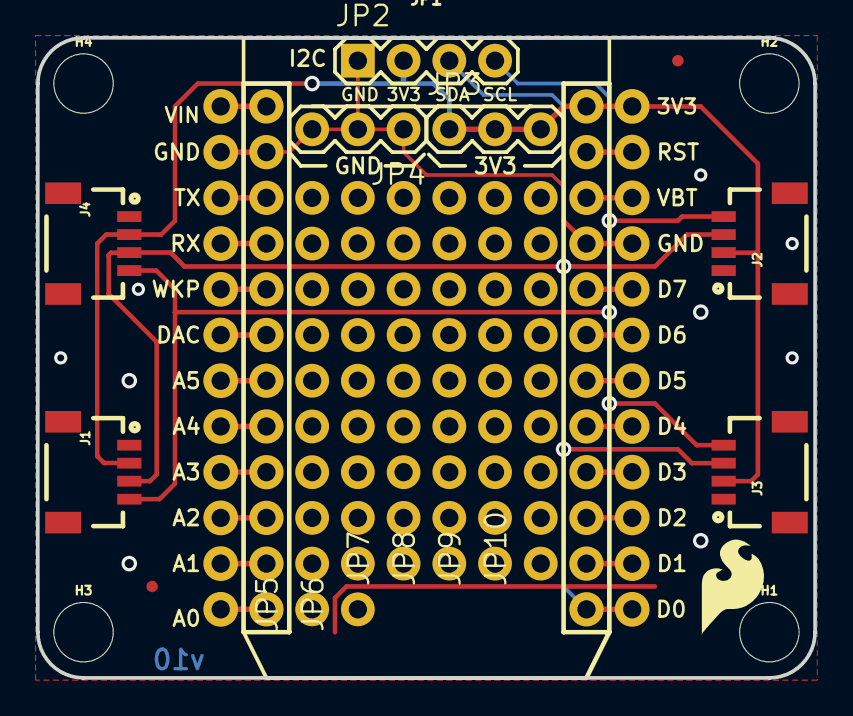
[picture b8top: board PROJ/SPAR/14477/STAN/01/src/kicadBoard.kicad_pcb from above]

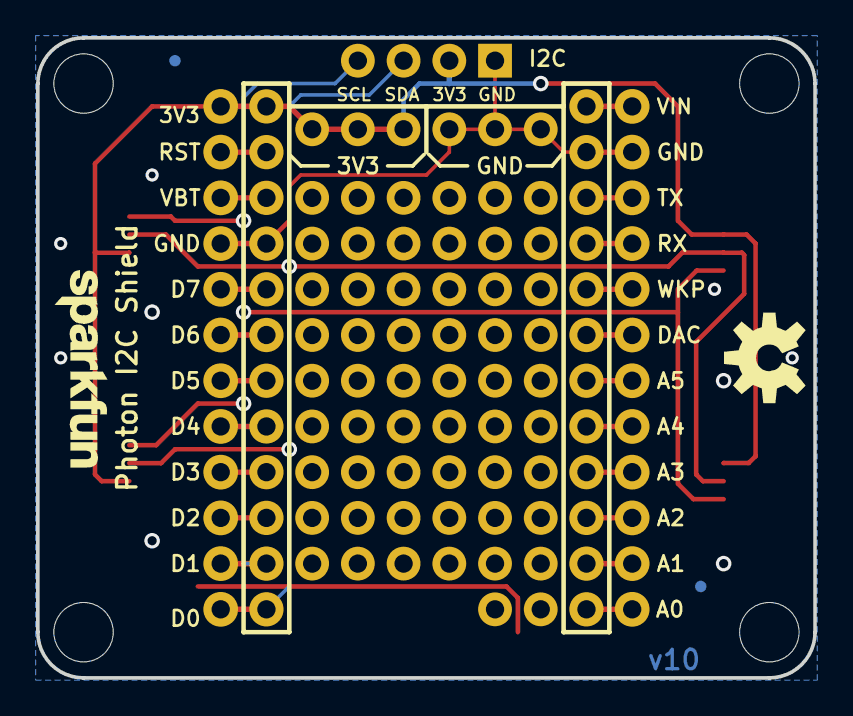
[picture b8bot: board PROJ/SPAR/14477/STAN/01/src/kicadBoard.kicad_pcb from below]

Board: 2 copper layers, 43.2 x 35.6 mm, 27 parts (4 on the bottom side), 23 nets.

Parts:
FD1, FD2, FD3, FD4: FIDUCIALUFIDUCIAL; FIDUCIAL-MICRO
FRAME1: FRAME-LETTER; CREATIVE_COMMONS
H1, H2, H3, H4: STAND-OFF
J1, J2, J3, J4: 1X04_1MM_RA
JP1: PARTICLE_PHOTONTEMPLATE_NO_STANDOFF; PARTICLE_PHOTON_TEMPLATE_NO_STANDOFF
JP2: 1X04
JP3, JP4: 1X03
JP5, JP6: 1X10_NO_SILK
JP7, JP8, JP9, JP10: 1X09_NO_SILK
LOGO1: OSHW-LOGOM; OSHW-LOGO-M
LOGO2: REVISION
U$1: SFE_LOGO_FLAME_.2
U$4: SFE_LOGO_NAME.1_INCH; SFE_LOGO_NAME_.1

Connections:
A0: JP1.12, JP1.A0
A1: JP1.11, JP1.A1
A2: JP1.10, JP1.A2
A3: JP1.9, JP1.A3
A4: JP1.8, JP1.A4
A5: JP1.7, JP1.A5
D2: JP1.15, JP1.D2
D3: JP1.16, JP1.D3
D4: JP1.17, JP1.D4
D5: JP1.18, JP1.D5
D6: JP1.19, JP1.D6
D7: JP1.20, JP1.D7
DAC: JP1.6, JP1.DAC
GND: J1.1, J2.1, J3.1, J4.1, JP1.2, JP1.21, JP1.GND@0, JP1.GND@2, JP2.1, JP4.1, JP4.2, JP4.3
RST: JP1.23, JP1.RST
RX: JP1.4, JP1.RX
SCL: J1.4, J2.4, J3.4, J4.4, JP1.14, JP1.D1, JP2.4
SDA: J1.3, J2.3, J3.3, J4.3, JP1.13, JP1.D0, JP2.3
TX: JP1.3, JP1.TX
VBAT: JP1.22, JP1.VBAT
VCC: J1.2, J2.2, J3.2, J4.2, JP1.3V3, JP1.24, JP2.2, JP3.1, JP3.2, JP3.3
VIN: JP1.1, JP1.VIN
WKP: JP1.5, JP1.WKP

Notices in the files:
parts and their libraries:
HTTPS://CREATIVECOMMONS.ORG/LICENSES/BY-SA/4.0
RELEASED UNDER THE CREATIVE COMMONS ATTRIBUTION SHARE-ALIKE 4.0 LICENSE
